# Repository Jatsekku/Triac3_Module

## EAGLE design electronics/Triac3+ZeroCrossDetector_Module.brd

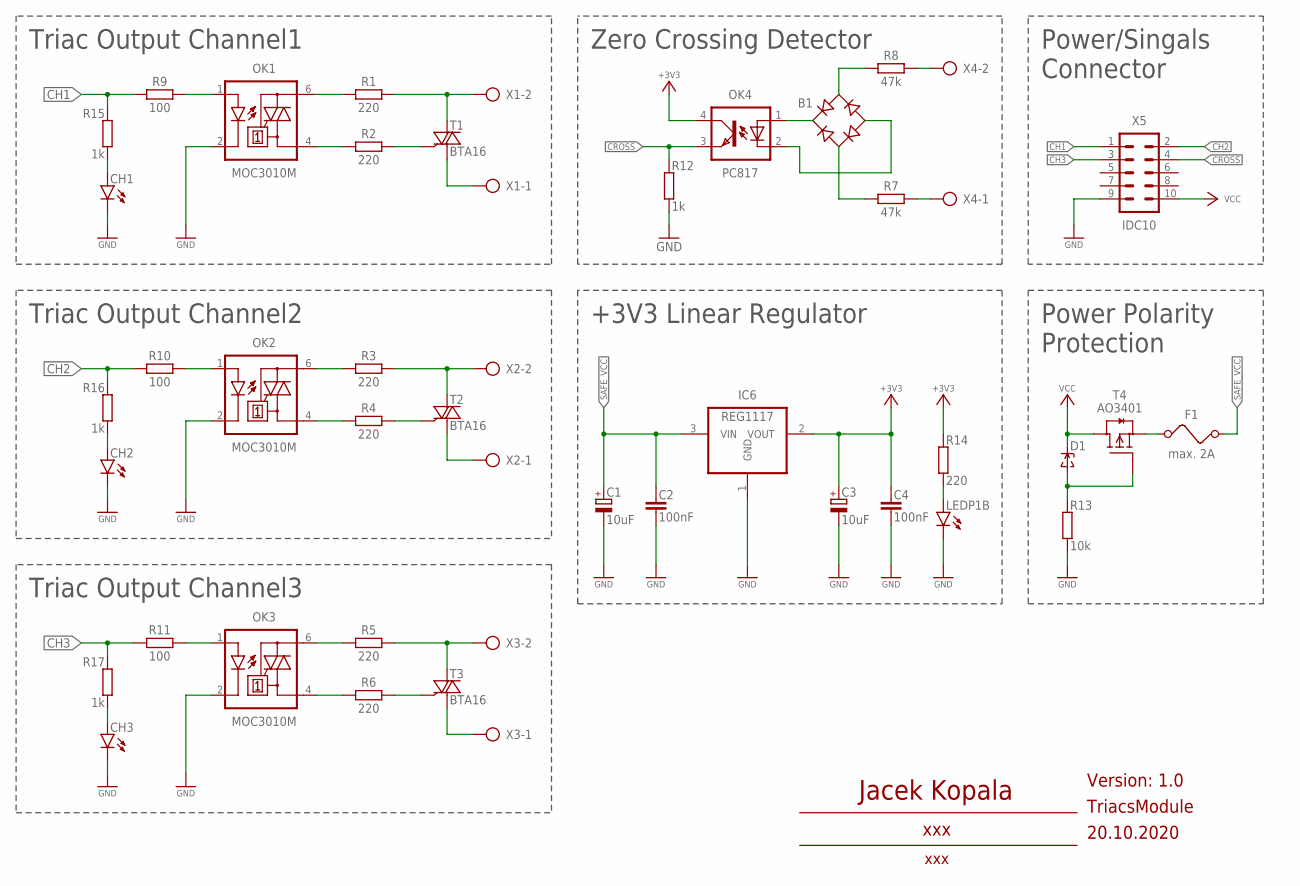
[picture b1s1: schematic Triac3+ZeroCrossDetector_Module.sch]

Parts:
B1: RB1A
C1, C3: 10uF; 153CLV-0405
C2, C4: 100nF; C0805
CH1, CH2, CH3: LEDCHIPLED_0805; CHIPLED_0805
D1: ZENERSOD-323F; SOD-323F
F1: max. 2A; 0805
IC6: REG1117; SOT223
LEDP1: LSG-T676; WL-SFCW-0603
OK1, OK2, OK3: MOC3010M; DIL06
OK4: PC817; DIL04
R1, R2, R3, R4, R5, R6: 220; 0204/7
R7, R8: 47k; 0207/10
R9, R10, R11: 100; R0805
R12, R15, R16, R17: 1k; R0805
R13: 10k; R0805
R14: 220; R0805
T1, T2, T3: BTA16; TO220BV
T4: AO3401; SOT23
X1, X2, X3, X4: TERMINAL7.5
X5: IDC10; ML10

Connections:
+3V3: C3.+, C4.1, IC6.2 (VOUT), OK4.4 (COL), R14.2
AC: R1.2, T1.T2 (A2), X1.2
AC1: R3.2, T2.T2 (A2), X2.2
AC2: R5.2, T3.T2 (A2), X3.2
CH1: R9.2, R15.1, X5.1
CH2: R10.2, R16.1, X5.2
CH3: R11.2, R17.1, X5.3
CROSS: OK4.3 (EMIT), R12.2, X5.4
GND: C1.-, C2.2, C3.-, C4.2, CH1.C, CH2.C, CH3.C, IC6.1 (GND), LEDP1.P$3 (C), OK1.2 (C), OK2.2 (C), OK3.2 (C), R12.1, R13.1, X5.9
unnamed: B1.AC2, R7.2
unnamed: B1.AC1, R8.2
unnamed: B1.-, OK4.2 (C)
unnamed: B1.+, OK4.1 (A)
unnamed: D1.A, R13.2, T4.1 (G)
unnamed: F1.1, T4.2 (S)
unnamed: R2.2, T1.G
unnamed: OK1.1 (A), R9.1
unnamed: OK1.6 (A2), R1.1
unnamed: CH1.A, R15.2
unnamed: T1.T1 (A1), X1.1
unnamed: OK1.4 (A1), R2.1
unnamed: CH2.A, R16.2
unnamed: OK2.1 (A), R10.1
unnamed: OK2.6 (A2), R3.1
unnamed: R4.2, T2.G
unnamed: T2.T1 (A1), X2.1
unnamed: OK2.4 (A1), R4.1
unnamed: CH3.A, R17.2
unnamed: OK3.1 (A), R11.1
unnamed: OK3.6 (A2), R5.1
unnamed: R6.2, T3.G
unnamed: T3.T1 (A1), X3.1
unnamed: OK3.4 (A1), R6.1
unnamed: R8.1, X4.2
unnamed: R7.1, X4.1
unnamed: LEDP1.P$4 (A), R14.1
SAFE_VCC: C1.+, C2.1, F1.2, IC6.3 (VIN)
VCC: D1.C, T4.3 (D), X5.10

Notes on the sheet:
Power Polarity Protection
+3V3 Linear Regulator
Triac Output Channel1
Triac Output Channel2
Triac Output Channel3
Zero Crossing Detector
Power/Singals Connector
Jacek Kopala
xxx
Version: 1.0
TriacsModule
20.10.2020

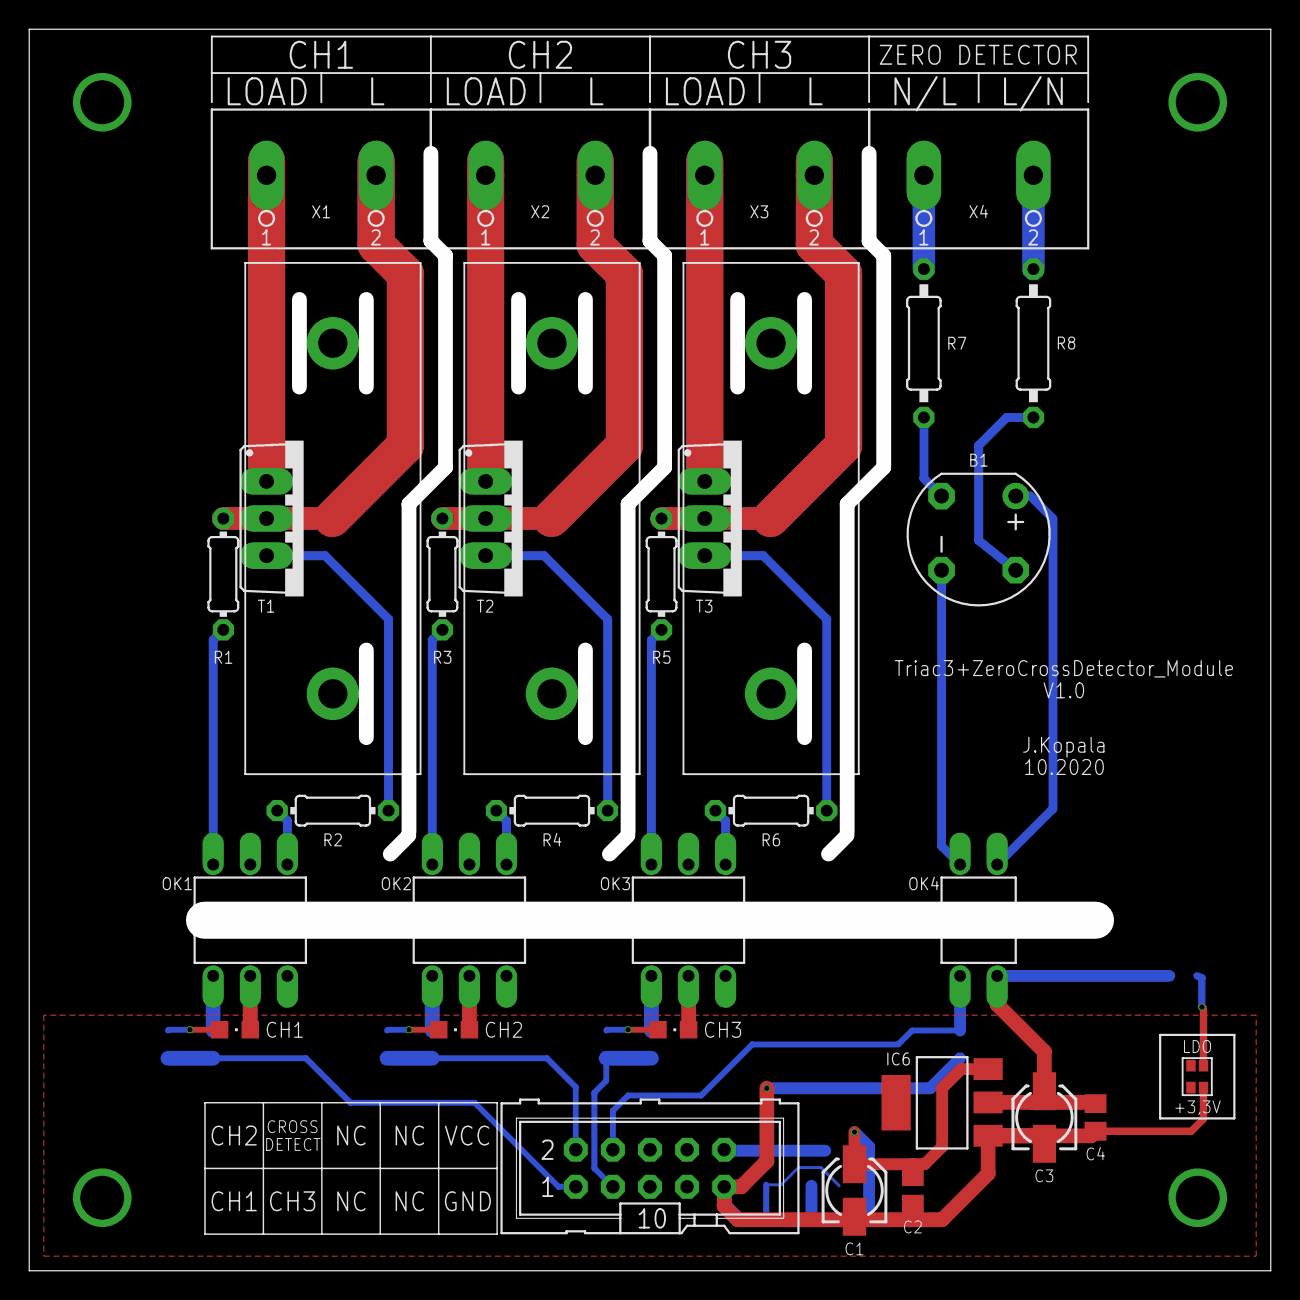
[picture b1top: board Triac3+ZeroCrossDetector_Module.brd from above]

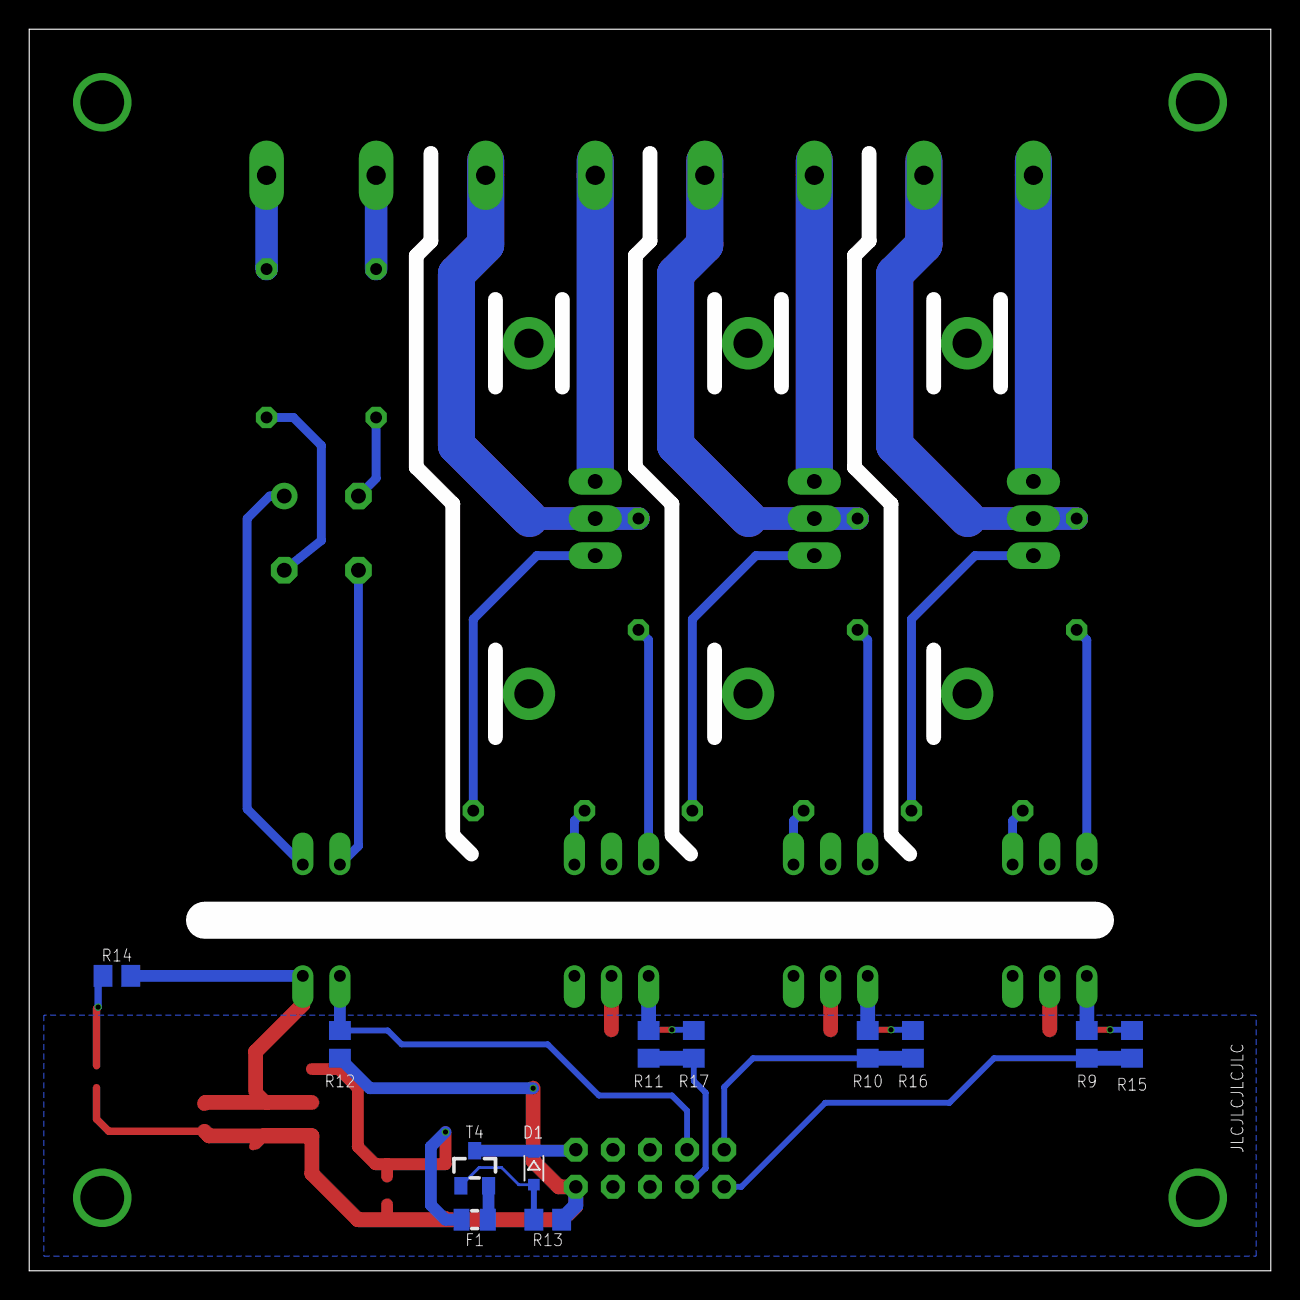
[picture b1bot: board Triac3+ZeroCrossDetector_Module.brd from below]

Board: 2 copper layers, 82.5 x 82.5 mm, 42 parts (12 on the bottom side), 38 nets.

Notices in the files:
parts and their libraries:
m-pad-2.1: License : GNU General Public License version 2 (see bottom)
